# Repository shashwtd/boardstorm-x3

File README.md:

## BoardStorm X3

this is a custom RP2040 microcontroller devboard, it comes with the following features

- USB-C power and programming
- 2MB onboard SPI flash
- 12MHz crystal oscillator
- broken out GPIO headers (Pico-compatible pinout)
- LiPo battery support with USB-C charging
- automatic USB/battery power switching via BQ24075
- can charge and run at once on USB power
- MAX17048 fuel gauge for accurate battery percentage over I2C

### key components used

- [RP2040](https://www.raspberrypi.com/products/rp2040/) — dual-core ARM Cortex-M0+ microcontroller
- [BQ24075RGT](https://www.ti.com/product/BQ24075) — USB Li-ion charger and power-path manager (USB/battery switching)
- [MAX17048G+T10](https://www.analog.com/en/products/max17048.html) — 1-cell fuel gauge (battery % over I2C)
- [MCP1700-330](https://www.microchip.com/en-us/product/mcp1700) — 3.3 V low-quiescent LDO regulator
- [W25Q16JVSS](https://www.winbond.com/hq/product/code-storage-flash-memory/serial-nor-flash/?__locale=en&partNo=W25Q16JV) — 16 Mbit (2 MB) SPI flash

---

### some things to keep in mind:
- `MAX17048` fuel gauge chip uses `GPIO4` and `GPIO5` to talk to the RP2040. It uses fixed I2C address `0x36`, so don't add another `0x36` I2C device.
- keep decoupling capacitors close to the chips during PCB layout.

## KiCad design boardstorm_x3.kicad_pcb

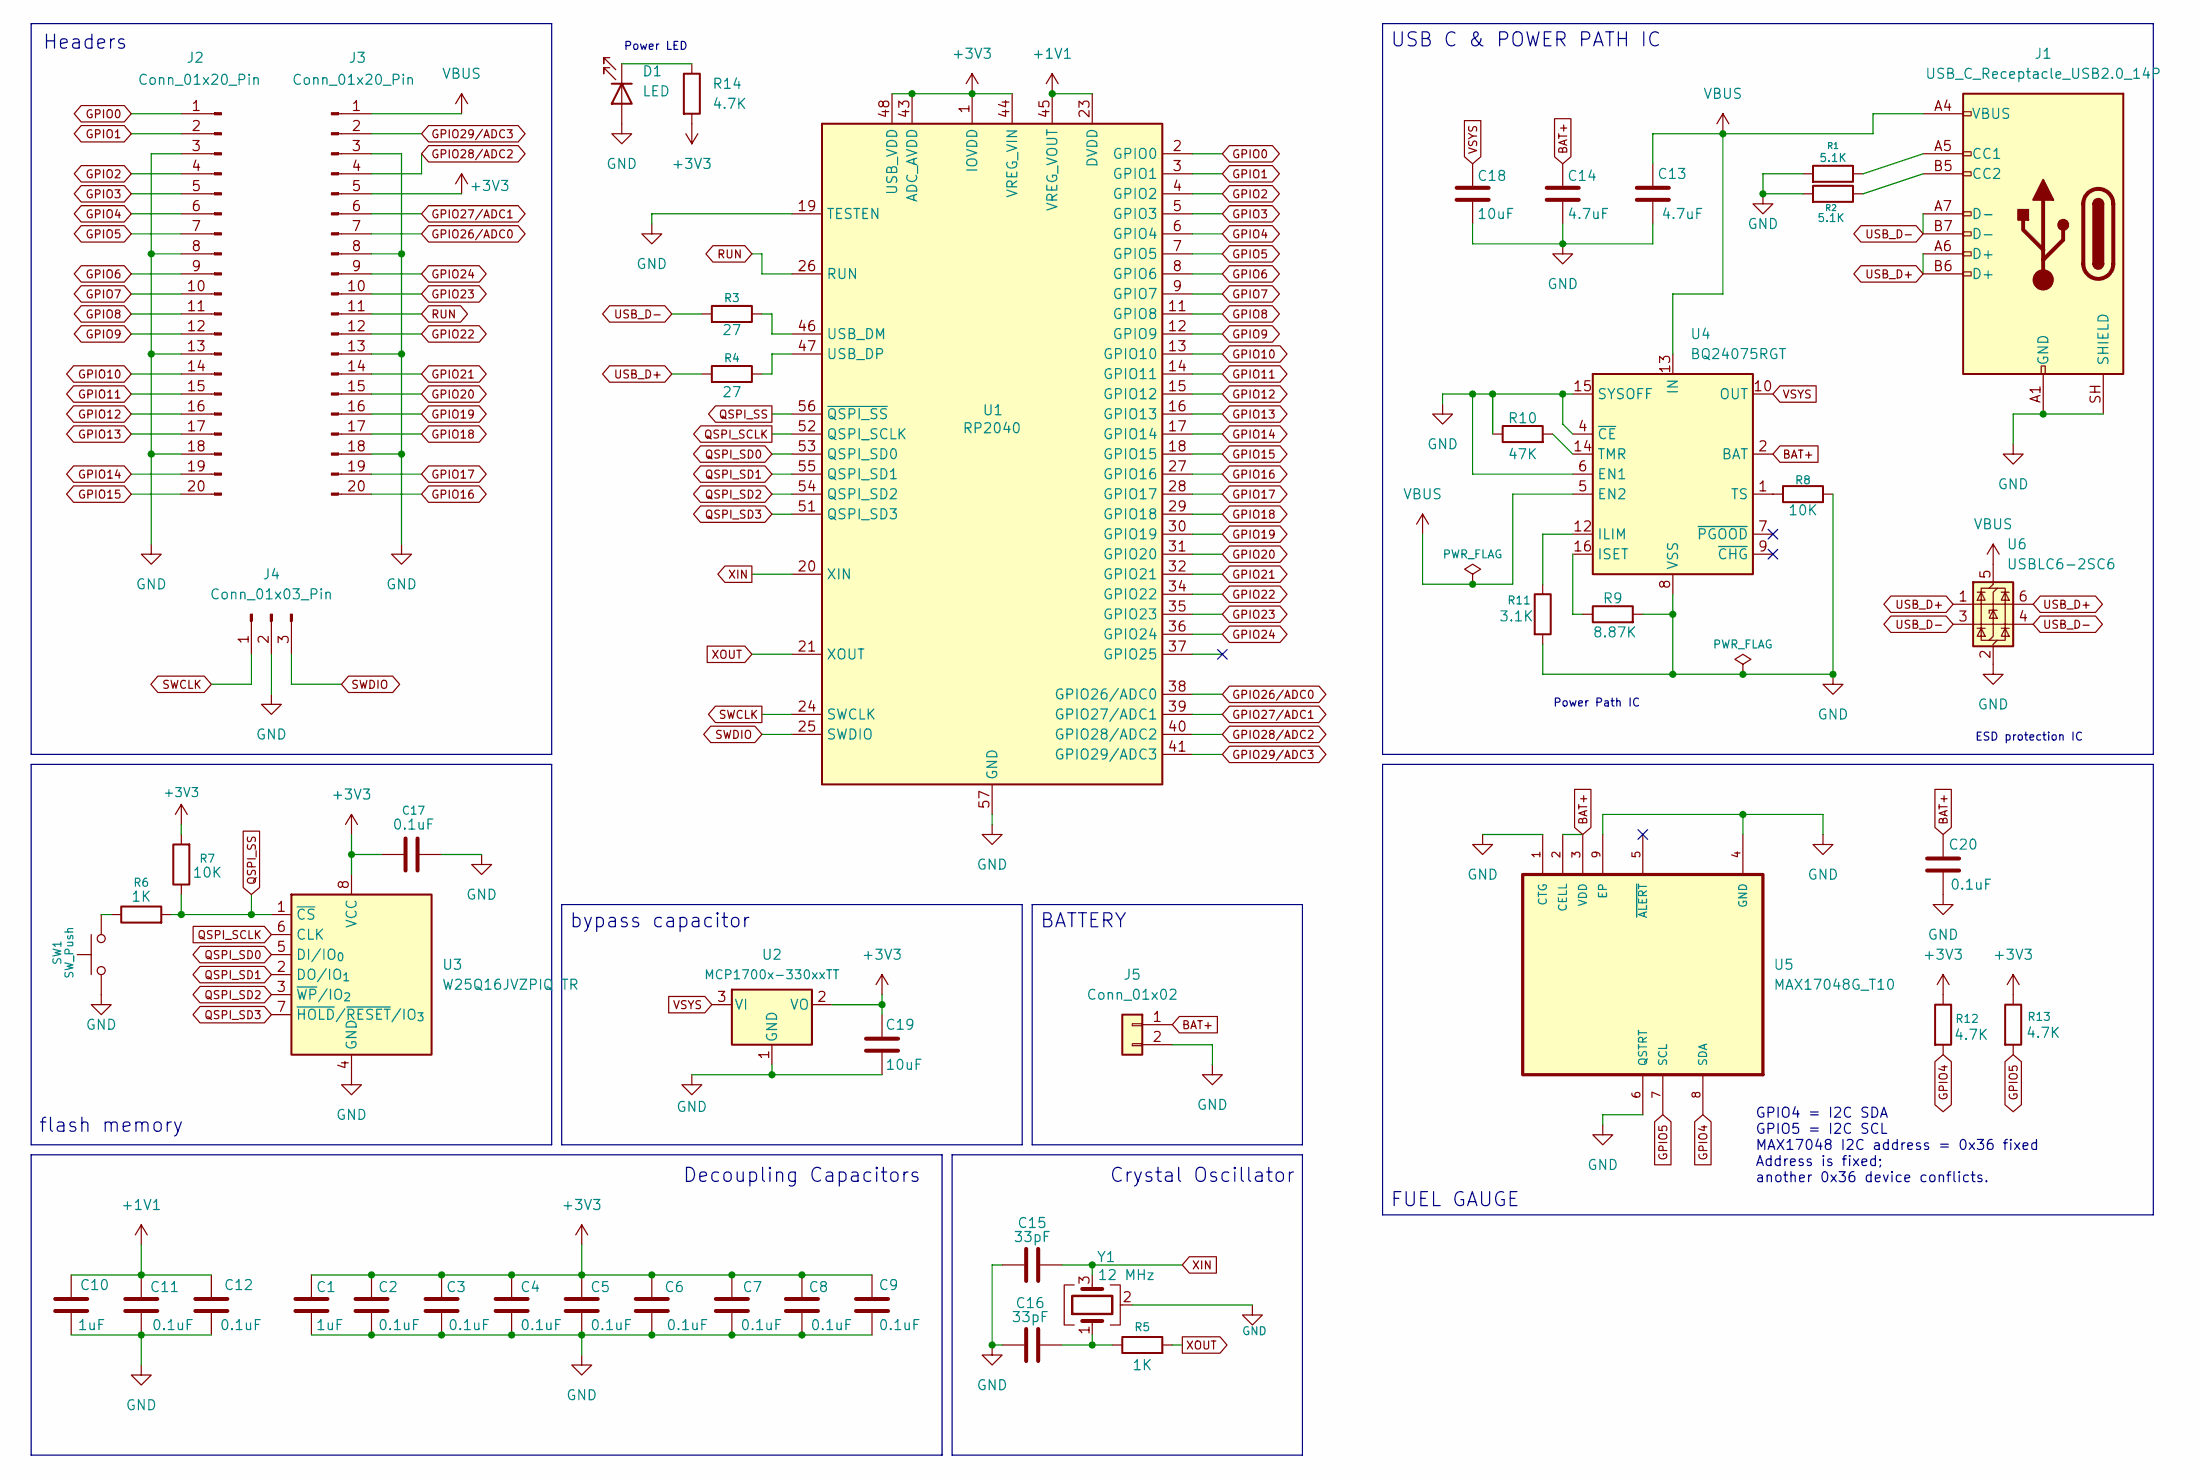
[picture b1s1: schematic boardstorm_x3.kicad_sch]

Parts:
C1, C10: 1uF; C_0402_1005Metric
C2, C3, C4, C5, C6, C7, C8, C9, C11, C12, C17, C20: 0.1uF; C_0402_1005Metric
C13, C14: 4.7uF; C_0603_1608Metric
C15, C16: 33pF; C_0402_1005Metric
C18, C19: 10uF; C_0603_1608Metric
D1: LED; LED_0402_1005Metric
J1: USB_C_Receptacle_USB2.0_14P; USB_C_Receptacle_HRO_TYPE-C-31-M-12
J2, J3: Conn_01x20_Pin; PinHeader_1x20_P2.54mm_Vertical
J4: Conn_01x03_Pin; PinHeader_1x03_P2.54mm_Vertical
J5: Conn_01x02; JST_PH_B2B-PH-K_1x02_P2.00mm_Vertical
R1, R2: 5.1K; R_0402_1005Metric
R3, R4: 27; R_0402_1005Metric
R5, R6: 1K; R_0402_1005Metric
R7, R8: 10K; R_0402_1005Metric
R9: 8.87K; R_0402_1005Metric
R10: 47K; R_0402_1005Metric
R11: 3.1K; R_0402_1005Metric
R12, R13, R14: 4.7K; R_0402_1005Metric
SW1: SW_Push; SW_Push_SPST_NO_Alps_SKRK
U1: RP2040; QFN-56-1EP_7x7mm_P0.4mm_EP3.2x3.2mm
U2: MCP1700x-330xxTT; SOT-23
U3: W25Q16JVZPIQ TR; Winbond_USON-8-1EP_3x2mm_P0.5mm_EP0.2x1.6mm
U4: BQ24075RGT; VQFN-16-1EP_3x3mm_P0.5mm_EP1.6x1.6mm
U5: MAX17048G_T10; 21-0168E_T822-3_MXM; DigiKey_Part_Number MAX17048G+T10CT-ND
U6: USBLC6-2SC6; SOT23-6L_STM-L
Y1: 12 MHz; Crystal_SMD_3225-4Pin_3.2x2.5mm

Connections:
+1V1: C10.1, C11.1, C12.1, U1.23 (DVDD), U1.45 (VREG_VOUT), U1.50 (DVDD)
+3V3: C1.1, C2.1, C3.1, C4.1, C5.1, C6.1, C7.1, C8.1, C9.1, C17.1, C19.1, J3.5, R7.2, R12.1, R13.1, R14.2, U1.1 (IOVDD), U1.10 (IOVDD), U1.22 (IOVDD), U1.33 (IOVDD), U1.42 (IOVDD), U1.43 (ADC_AVDD), U1.44 (VREG_VIN), U1.48 (USB_VDD), U1.49 (IOVDD), U2.2 (VO), U3.8 (VCC)
BAT+: C14.1, C20.1, J5.1, U4.2 (BAT), U4.3 (BAT), U5.2 (CELL), U5.3 (VDD)
GND: C1.2, C2.2, C3.2, C4.2, C5.2, C6.2, C7.2, C8.2, C9.2, C10.2, C11.2, C12.2, C13.2, C14.2, C15.1, C16.1, C17.2, C18.2, C19.2, C20.2, D1.2 (A), J1.A1 (GND), J1.A12 (GND), J1.B1 (GND), J1.B12 (GND), J1.SH (SHIELD), J2.3, J2.8, J2.13, J2.18, J3.3, J3.8, J3.13, J3.18, J4.2, J5.2, R1.2, R2.2, R8.2, R9.2, R10.1, R11.2, SW1.1, U1.19 (TESTEN), U1.57 (GND), U2.1 (GND), U3.4 (GND), U4.4 (~CE), U4.6 (EN1), U4.8 (VSS), U4.15 (SYSOFF), U4.17 (VSS), U5.1 (CTG), U5.4 (GND), U5.6 (QSTRT), U5.9 (EP), U6.2 (GND), Y1.2 (G), Y1.4 (G)
GPIO0: J2.1, U1.2 (GPIO0)
GPIO1: J2.2, U1.3 (GPIO1)
GPIO2: J2.4, U1.4 (GPIO2)
GPIO3: J2.5, U1.5 (GPIO3)
GPIO4: J2.6, R12.2, U1.6 (GPIO4), U5.8 (SDA)
GPIO5: J2.7, R13.2, U1.7 (GPIO5), U5.7 (SCL)
GPIO6: J2.9, U1.8 (GPIO6)
GPIO7: J2.10, U1.9 (GPIO7)
GPIO8: J2.11, U1.11 (GPIO8)
GPIO9: J2.12, U1.12 (GPIO9)
GPIO10: J2.14, U1.13 (GPIO10)
GPIO11: J2.15, U1.14 (GPIO11)
GPIO12: J2.16, U1.15 (GPIO12)
GPIO13: J2.17, U1.16 (GPIO13)
GPIO14: J2.19, U1.17 (GPIO14)
GPIO15: J2.20, U1.18 (GPIO15)
GPIO16: J3.20, U1.27 (GPIO16)
GPIO17: J3.19, U1.28 (GPIO17)
GPIO18: J3.17, U1.29 (GPIO18)
GPIO19: J3.16, U1.30 (GPIO19)
GPIO20: J3.15, U1.31 (GPIO20)
GPIO21: J3.14, U1.32 (GPIO21)
GPIO22: J3.12, U1.34 (GPIO22)
GPIO23: J3.10, U1.35 (GPIO23)
GPIO24: J3.9, U1.36 (GPIO24)
GPIO26/ADC0: J3.7, U1.38 (GPIO26/ADC0)
GPIO27/ADC1: J3.6, U1.39 (GPIO27/ADC1)
GPIO28/ADC2: J3.4, U1.40 (GPIO28/ADC2)
GPIO29/ADC3: J3.2, U1.41 (GPIO29/ADC3)
unnamed: C16.2, R5.1, Y1.1
unnamed: D1.1 (K), R14.1
unnamed: J1.A5 (CC1), R1.1
unnamed: J1.B5 (CC2), R2.1
unnamed: R6.1, SW1.2
unnamed: R3.1, U1.46 (USB_DM)
unnamed: R4.1, U1.47 (USB_DP)
unnamed: R11.1, U4.12 (ILIM)
unnamed: R9.1, U4.16 (ISET)
unnamed: R10.2, U4.14 (TMR)
unnamed: R8.1, U4.1 (TS)
QSPI_SCLK: U1.52 (QSPI_SCLK), U3.6 (CLK)
QSPI_SD0: U1.53 (QSPI_SD0), U3.5 (DI/IO_{0})
QSPI_SD1: U1.55 (QSPI_SD1), U3.2 (DO/IO_{1})
QSPI_SD2: U1.54 (QSPI_SD2), U3.3 (~WP/IO_{2})
QSPI_SD3: U1.51 (QSPI_SD3), U3.7 (~HOLD/~RESET/IO_{3})
QSPI_SS: R6.2, R7.1, U1.56 (~QSPI_SS), U3.1 (~CS)
RUN: J3.11, U1.26 (RUN)
SWCLK: J4.1, U1.24 (SWCLK)
SWDIO: J4.3, U1.25 (SWDIO)
USB_D+: J1.A6 (D+), J1.B6 (D+), R4.2, U6.1 (I/O1), U6.6 (I/O1)
USB_D-: J1.A7 (D-), J1.B7 (D-), R3.2, U6.3 (I/O2), U6.4 (I/O2)
VBUS: C13.1, J1.A4 (VBUS), J1.A9 (VBUS), J1.B4 (VBUS), J1.B9 (VBUS), J3.1, U4.5 (EN2), U4.13 (IN), U6.5 (VBUS)
VSYS: C18.1, U2.3 (VI), U4.10 (OUT), U4.11 (OUT)
XIN: C15.2, U1.20 (XIN), Y1.3
XOUT: R5.2, U1.21 (XOUT)

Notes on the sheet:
flash memory
Crystal Oscillator
Decoupling Capacitors
Headers
GPIO4 = I2C SDA GPIO5 = I2C SCL MAX17048 I2C address = 0x36 fixed Address is fixed; another 0x36 device conflicts.
Power LED
ESD protection IC
Power Path IC
USB C & POWER PATH IC
FUEL GAUGE
bypass capacitor
BATTERY

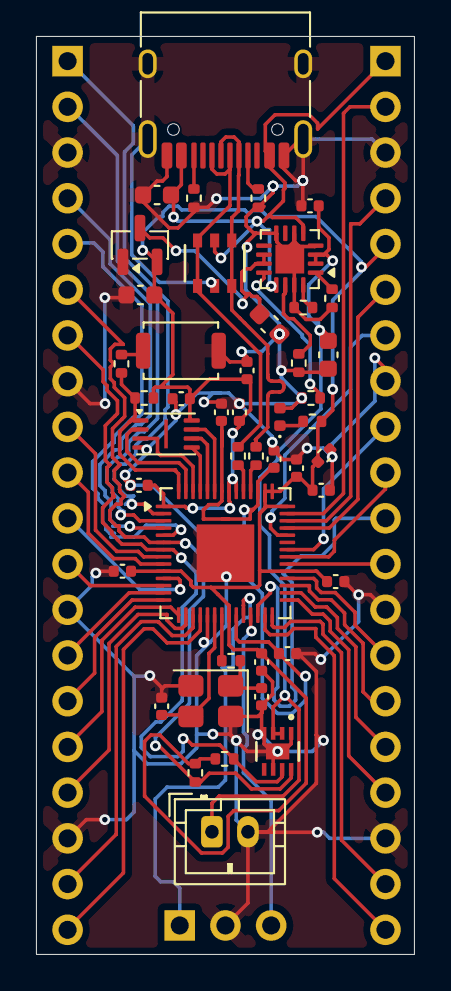
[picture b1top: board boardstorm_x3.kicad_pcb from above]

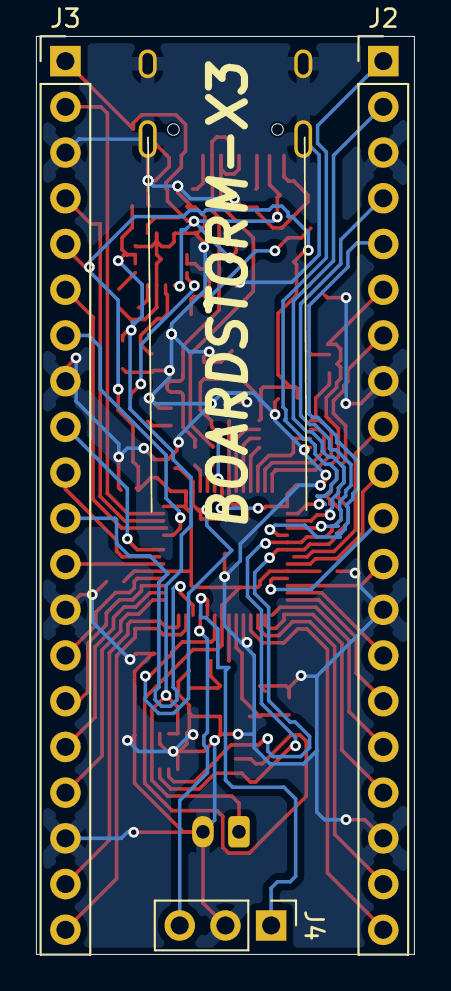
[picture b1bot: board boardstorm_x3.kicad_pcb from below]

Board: 2 copper layers, 21.0 x 51.0 mm, 48 parts (3 on the bottom side), 59 nets.

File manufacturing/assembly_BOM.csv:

"Reference","Qty","Value","Footprint","DigiKey_Part_Number","MF","MP","Package","LCSC Part #","Assembly Note"
"C1,C10","2","1uF","Capacitor_SMD:C_0402_1005Metric","","Samsung","CL05A105KA5NQNC","0402","C52923","1uF 25V X5R MLCC"
"C2,C3,C4,C5,C6,C7,C8,C9,C11,C12,C17,C20","12","0.1uF","Capacitor_SMD:C_0402_1005Metric","","Samsung","CL05B104KO5NNNC","0402","C1525","100nF 16V X7R MLCC"
"C13,C14","2","4.7uF","Capacitor_SMD:C_0603_1608Metric","","Samsung","CL10A475KO8NNNC","0603","C19666","4.7uF 16V X5R MLCC"
"C15,C16","2","33pF","Capacitor_SMD:C_0402_1005Metric","","FH","0402CG330J500NT","0402","C1562","33pF 50V C0G/NP0 crystal load cap"
"C18,C19","2","10uF","Capacitor_SMD:C_0603_1608Metric","","Samsung","CL10A106KP8NNNC","0603","C19702","10uF 10V X5R MLCC"
"D1","1","Red LED","LED_SMD:LED_0402_1005Metric","","NationStar","NCD0402R1","0402","C130719","0402 red indicator LED"
"J1","1","TYPE-C-31-M-12","Connector_USB:USB_C_Receptacle_HRO_TYPE-C-31-M-12","","Korean Hroparts Elec","TYPE-C-31-M-12","USB-C SMD 16P","C165948","Exact KiCad footprint match"
"J2,J3","2","Conn_01x20_Pin","Connector_PinHeader_2.54mm:PinHeader_1x20_P2.54mm_Vertical","","","","","","Do not assemble; hand-solder headers"
"J4","1","Conn_01x03_Pin","Connector_PinHeader_2.54mm:PinHeader_1x03_P2.54mm_Vertical","","","","","","Do not assemble; hand-solder SWD header"
"J5","1","B2B-PH-K-S(LF)(SN)","Connector_JST:JST_PH_B2B-PH-K_1x02_P2.00mm_Vertical","","JST","B2B-PH-K-S(LF)(SN)","JST-PH 2P vertical THT","C131337","Verify battery cable polarity before use"
"R1,R2","2","5.1K","Resistor_SMD:R_0402_1005Metric","","UNI-ROYAL","0402WGF5101TCE","0402","C25905","1% USB-C CC pulldown"
"R3,R4","2","27","Resistor_SMD:R_0402_1005Metric","","Yageo","RC0402FR-0727RL","0402","C138021","1% USB D+/D- series resistor"
"R5,R6","2","1K","Resistor_SMD:R_0402_1005Metric","","UNI-ROYAL","0402WGF1001TCE","0402","C11702","1%"
"R7,R8","2","10K","Resistor_SMD:R_0402_1005Metric","","UNI-ROYAL","0402WGF1002TCE","0402","C25744","1%"
"R9","1","8.87K","Resistor_SMD:R_0402_1005Metric","","UNI-ROYAL","0402WGF8871TCE","0402","C36953","1% BQ24075 ISET"
"R10","1","47K","Resistor_SMD:R_0402_1005Metric","","UNI-ROYAL","0402WGF4702TCE","0402","C25792","1%"
"R11","1","3.09K","Resistor_SMD:R_0402_1005Metric","","UNI-ROYAL","0402WGF3091TCE","0402","C11460","1%; used instead of nominal 3.1K"
"R12,R13,R14","3","4.7K","Resistor_SMD:R_0402_1005Metric","","UNI-ROYAL","0402WGF4701TCE","0402","C25900","1%"
"SW1","1","TS-1088-AR02016","Button_Switch_SMD:SW_Push_SPST_NO_Alps_SKRK","","XUNPU","TS-1088-AR02016","SMD 4x3mm tactile","C720477","Close match to Alps SKRK footprint; verify JLC preview"
"U1","1","RP2040","Package_DFN_QFN:QFN-56-1EP_7x7mm_P0.4mm_EP3.2x3.2mm","","Raspberry Pi","RP2040","LQFN-56 7x7mm","C2040",""
"U2","1","MCP1700T-3302E/TT","Package_TO_SOT_SMD:SOT-23","","Microchip","MCP1700T-3302E/TT","SOT-23-3","C39051","3.3V LDO"
"U3","1","W25Q16JVUXIQ","Package_SON:Winbond_USON-8-1EP_3x2mm_P0.5mm_EP0.2x1.6mm","","Winbond","W25Q16JVUXIQ","USON-8-EP 2x3mm","C2843335","Corrects prior ZPIQ/WSON package mismatch"
"U4","1","BQ24075RGTR","Package_DFN_QFN:VQFN-16-1EP_3x3mm_P0.5mm_EP1.6x1.6mm","","Texas Instruments","BQ24075RGTR","QFN-16-EP 3x3mm","C15464","Tape/reel orderable form of BQ24075RGT"
"U5","1","MAX17048G+T10","MAX17048G_T10:21-0168E_T822-3_MXM","MAX17048G+T10CT-ND","Analog Devices/Maxim","MAX17048G+T10","DFN-8-EP 2x2mm","C2682616",""
"U6","1","USBLC6-2SC6","USBLC6_2SC6:SOT23-6L_STM-L","","STMicroelectronics","USBLC6-2SC6","SOT-23-6L","C7519","Do not substitute USBLC6-2P6"
"Y1","1","12 MHz","Crystal:Crystal_SMD_3225-4Pin_3.2x2.5mm","","YXC","X322512MSB4SI","SMD3225-4P","C9002","12MHz 20pF crystal"

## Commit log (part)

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2026-05-25 setting up the project structure
2026-05-25 cleared up the journal file
2026-05-25 setup a kicad project
2026-05-25 worked on capacitors, wiring and usb c
2026-05-26 setting up a crystal oscillator system, studied more about usbc power and the clock mechanism in such tiny boards.
2026-05-26 done with flash storage & more progress YAHOO
2026-05-26 added header pin symbols & finished up the schematic design
2026-05-27 fixed a few issues/typos
2026-05-27 planned it out
2026-05-28 making some progress... using a power path with the usb c input
2026-05-28 journal update commit
2026-05-28 backing up
2026-05-28 added decoupling capacitors & voltage regulator
2026-05-28 added the fuel gauge, any assets related to it, and journal
2026-05-28 fixing a bunch of ERC issues
2026-05-28 organized schematic design,, added some notes to readme, updated journal
2026-05-29 assigned footprints & updated README
2026-05-29 some basic PCB design & journals wohoo
2026-05-29 some more pcb updates
2026-05-30 wow good progress shash
2026-05-30 journal
2026-05-30 pitstop
2026-05-30 Add automated schematic design review
    Ran the boardstorm-x3 schematic through PromptPCB, an automated PCB design
    review tool that downloads real datasheets from JLCPCB and cross-references
    every pin connection against the specs.
    Results: 5 errors, 6 warnings, 3 suggestions, 19 verified checks.
    Key findings:
    - MAX17048 I2C pull-ups reference +3V3 but fuel gauge VDD is on BAT+
2026-05-31 pcb update & more journals.. still fixing routes
2026-06-01 added ESD protection IC, updated 3d models, fixed some wiring, added a power LED,
2026-06-01 i did someting but i forgot
2026-06-15 added images for the devboard
2026-06-15 Fix image paths in README.md
    Updated image paths in README.md to use forward slashes instead of windows method
2026-06-27 fix markdown image rendering
2026-06-27 added time spend for each day
2026-06-27 update readme images
2026-06-27 added BOM and any other manufacturing related details...
2026-06-29 fixed image rendering
